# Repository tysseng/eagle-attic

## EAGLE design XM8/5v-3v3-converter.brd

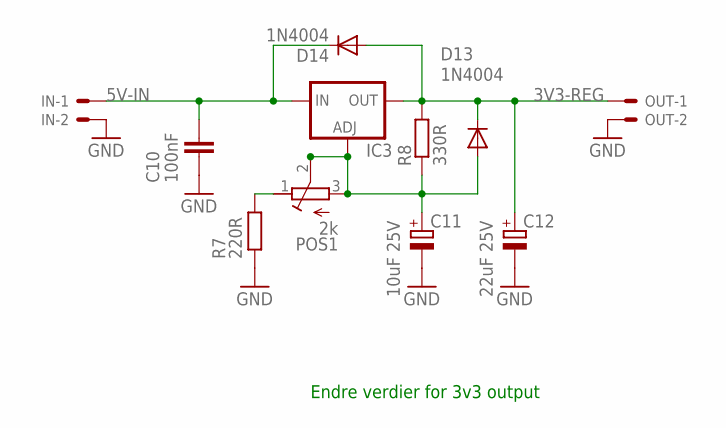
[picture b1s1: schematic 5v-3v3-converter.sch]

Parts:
C10: 100nF; C050-025X075
C11: 10uF 25V; E2,5-5
C12: 22uF 25V; E2,5-5
D13, D14: 1N4004; DO41-10
IC3: LM317TS; 317TS
IN: KK-156-2
OUT: KK-156-2
POS1: 2k; RTRIMT93YA
R7: 220R; 0207/7
R8: 330R; 0207/7

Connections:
3V3-REG: C12.+, D13.C, D14.A, IC3.2 (OUT), OUT.1, R8.2
5V-IN: C10.1, D14.C, IC3.3 (IN), IN.1
GND: C10.2, C11.-, C12.-, IN.2, OUT.2, R7.1
unnamed: POS1.1 (E), R7.2
unnamed: C11.+, D13.A, IC3.1 (ADJ), POS1.2 (S), POS1.3 (A), R8.1

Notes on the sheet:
Endre verdier for 3v3 output

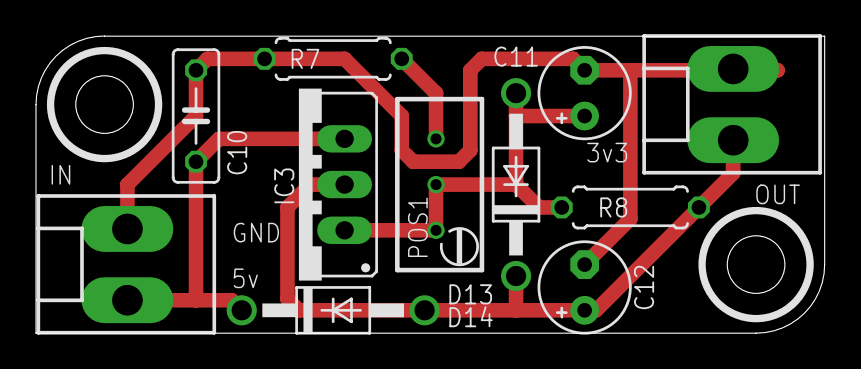
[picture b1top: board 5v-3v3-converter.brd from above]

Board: 2 copper layers, 43.8 x 16.5 mm, 11 parts (0 on the bottom side), 5 nets.

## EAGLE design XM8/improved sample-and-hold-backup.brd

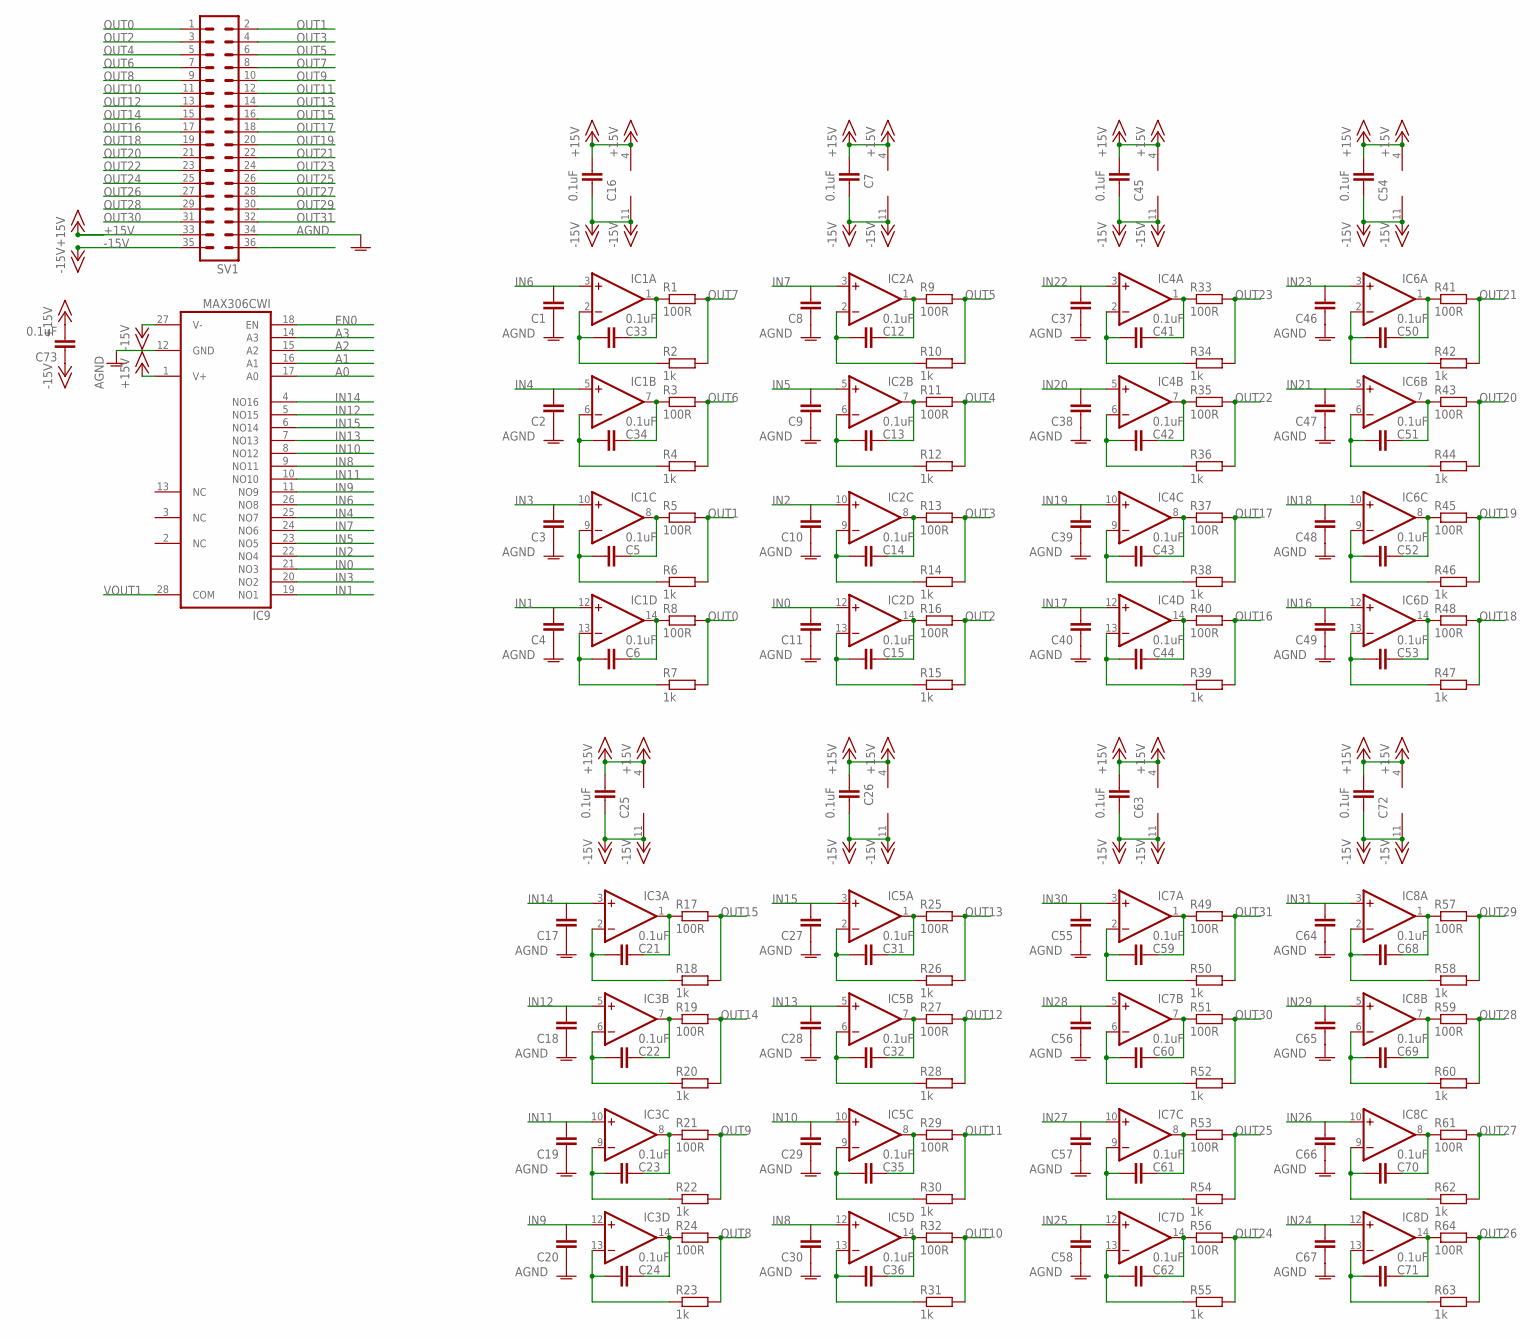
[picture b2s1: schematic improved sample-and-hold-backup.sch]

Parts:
C1, C2, C3, C4, C8, C9, C10, C11, C17, C18, C19, C20, C27, C28, C29, C30, C37, C38, C39, C40, C46, C47, C48, C49, C55, C56, C57, C58, C64, C65, C66, C67: C-EUC1206; C1206
C5, C6, C7, C12, C13, C14, C15, C16, C21, C22, C23, C24, C25, C26, C31, C32, C33, C34, C35, C36, C41, C42, C43, C44, C45, C50, C51, C52, C53, C54, C59, C60, C61, C62, C63, C68, C69, C70, C71, C72, C73: 0.1uF; C0603
IC1, IC2, IC3, IC4, IC5, IC6, IC7, IC8: TL074D; SO14
IC9: MAX306CWI; SO28L
R1, R3, R5, R8, R9, R11, R13, R16, R17, R19, R21, R24, R25, R27, R29, R32, R33, R35, R37, R40, R41, R43, R45, R48, R49, R51, R53, R56, R57, R59, R61, R64: 100R; R0603
R2, R4, R6, R7, R10, R12, R14, R15, R18, R20, R22, R23, R26, R28, R30, R31, R34, R36, R38, R39, R42, R44, R46, R47, R50, R52, R54, R55, R58, R60, R62, R63: 1k; R0603
SV1: MA18-2

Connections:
+15V: C7.1, C16.1, C25.1, C26.1, C45.1, C54.1, C63.1, C72.1, C73.2, IC1.4 (V+), IC2.4 (V+), IC3.4 (V+), IC4.4 (V+), IC5.4 (V+), IC6.4 (V+), IC7.4 (V+), IC8.4 (V+), IC9.1 (V+), SV1.33
-15V: C7.2, C16.2, C25.2, C26.2, C45.2, C54.2, C63.2, C72.2, C73.1, IC1.11 (V-), IC2.11 (V-), IC3.11 (V-), IC4.11 (V-), IC5.11 (V-), IC6.11 (V-), IC7.11 (V-), IC8.11 (V-), IC9.27 (V-), SV1.35
A0: IC9.17 (A0)
A1: IC9.16 (A1)
A2: IC9.15 (A2)
A3: IC9.14 (A3)
AGND: C1.1, C2.1, C3.1, C4.1, C8.1, C9.1, C10.1, C11.1, C17.1, C18.1, C19.1, C20.1, C27.1, C28.1, C29.1, C30.1, C37.1, C38.1, C39.1, C40.1, C46.1, C47.1, C48.1, C49.1, C55.1, C56.1, C57.1, C58.1, C64.1, C65.1, C66.1, C67.1, IC9.12 (GND), SV1.34
EN0: IC9.18 (EN)
IN0: C11.2, IC2.12 (+IN), IC9.21 (NO3)
IN1: C4.2, IC1.12 (+IN), IC9.19 (NO1)
IN2: C10.2, IC2.10 (+IN), IC9.22 (NO4)
IN3: C3.2, IC1.10 (+IN), IC9.20 (NO2)
IN4: C2.2, IC1.5 (+IN), IC9.25 (NO7)
IN5: C9.2, IC2.5 (+IN), IC9.23 (NO5)
IN6: C1.2, IC1.3 (+IN), IC9.26 (NO8)
IN7: C8.2, IC2.3 (+IN), IC9.24 (NO6)
IN8: C30.2, IC5.12 (+IN), IC9.9 (NO11)
IN9: C20.2, IC3.12 (+IN), IC9.11 (NO9)
IN10: C29.2, IC5.10 (+IN), IC9.8 (NO12)
IN11: C19.2, IC3.10 (+IN), IC9.10 (NO10)
IN12: C18.2, IC3.5 (+IN), IC9.5 (NO15)
IN13: C28.2, IC5.5 (+IN), IC9.7 (NO13)
IN14: C17.2, IC3.3 (+IN), IC9.4 (NO16)
IN15: C27.2, IC5.3 (+IN), IC9.6 (NO14)
IN16: C49.2, IC6.12 (+IN)
IN17: C40.2, IC4.12 (+IN)
IN18: C48.2, IC6.10 (+IN)
IN19: C39.2, IC4.10 (+IN)
IN20: C38.2, IC4.5 (+IN)
IN21: C47.2, IC6.5 (+IN)
IN22: C37.2, IC4.3 (+IN)
IN23: C46.2, IC6.3 (+IN)
IN24: C67.2, IC8.12 (+IN)
IN25: C58.2, IC7.12 (+IN)
IN26: C66.2, IC8.10 (+IN)
IN27: C57.2, IC7.10 (+IN)
IN28: C56.2, IC7.5 (+IN)
IN29: C65.2, IC8.5 (+IN)
IN30: C55.2, IC7.3 (+IN)
IN31: C64.2, IC8.3 (+IN)
unnamed: C33.2, IC1.2 (-IN), R2.1
unnamed: C33.1, IC1.1 (OUT), R1.1
unnamed: C34.1, IC1.7 (OUT), R3.1
unnamed: C5.1, IC1.8 (OUT), R5.1
unnamed: C34.2, IC1.6 (-IN), R4.1
unnamed: C6.1, IC1.14 (OUT), R8.1
unnamed: C5.2, IC1.9 (-IN), R6.1
unnamed: C6.2, IC1.13 (-IN), R7.1
unnamed: C21.1, IC3.1 (OUT), R17.1
unnamed: C21.2, IC3.2 (-IN), R18.1
unnamed: C12.1, IC2.1 (OUT), R9.1
unnamed: C12.2, IC2.2 (-IN), R10.1
unnamed: C13.1, IC2.7 (OUT), R11.1
unnamed: C13.2, IC2.6 (-IN), R12.1
unnamed: C14.1, IC2.8 (OUT), R13.1
unnamed: C15.1, IC2.14 (OUT), R16.1
unnamed: C14.2, IC2.9 (-IN), R14.1
unnamed: C15.2, IC2.13 (-IN), R15.1
unnamed: C22.1, IC3.7 (OUT), R19.1
unnamed: C22.2, IC3.6 (-IN), R20.1
unnamed: C23.1, IC3.8 (OUT), R21.1
unnamed: C24.1, IC3.14 (OUT), R24.1
unnamed: C23.2, IC3.9 (-IN), R22.1
unnamed: C24.2, IC3.13 (-IN), R23.1
unnamed: C31.1, IC5.1 (OUT), R25.1
unnamed: C31.2, IC5.2 (-IN), R26.1
unnamed: C32.1, IC5.7 (OUT), R27.1
unnamed: C32.2, IC5.6 (-IN), R28.1
unnamed: C35.1, IC5.8 (OUT), R29.1
unnamed: C36.1, IC5.14 (OUT), R32.1
unnamed: C35.2, IC5.9 (-IN), R30.1
unnamed: C36.2, IC5.13 (-IN), R31.1
unnamed: C41.1, IC4.1 (OUT), R33.1
unnamed: C41.2, IC4.2 (-IN), R34.1
unnamed: C42.1, IC4.7 (OUT), R35.1
unnamed: C42.2, IC4.6 (-IN), R36.1
unnamed: C43.1, IC4.8 (OUT), R37.1
unnamed: C44.1, IC4.14 (OUT), R40.1
unnamed: C43.2, IC4.9 (-IN), R38.1
unnamed: C44.2, IC4.13 (-IN), R39.1
unnamed: C50.1, IC6.1 (OUT), R41.1
unnamed: C50.2, IC6.2 (-IN), R42.1
unnamed: C51.1, IC6.7 (OUT), R43.1
unnamed: C51.2, IC6.6 (-IN), R44.1
unnamed: C52.1, IC6.8 (OUT), R45.1
unnamed: C53.1, IC6.14 (OUT), R48.1
unnamed: C52.2, IC6.9 (-IN), R46.1
unnamed: C53.2, IC6.13 (-IN), R47.1
unnamed: C59.1, IC7.1 (OUT), R49.1
unnamed: C59.2, IC7.2 (-IN), R50.1
unnamed: C60.1, IC7.7 (OUT), R51.1
unnamed: C60.2, IC7.6 (-IN), R52.1
unnamed: C61.1, IC7.8 (OUT), R53.1
unnamed: C62.1, IC7.14 (OUT), R56.1
unnamed: C61.2, IC7.9 (-IN), R54.1
unnamed: C62.2, IC7.13 (-IN), R55.1
unnamed: C68.1, IC8.1 (OUT), R57.1
unnamed: C68.2, IC8.2 (-IN), R58.1
unnamed: C69.1, IC8.7 (OUT), R59.1
unnamed: C69.2, IC8.6 (-IN), R60.1
unnamed: C70.1, IC8.8 (OUT), R61.1
unnamed: C71.1, IC8.14 (OUT), R64.1
unnamed: C70.2, IC8.9 (-IN), R62.1
unnamed: C71.2, IC8.13 (-IN), R63.1
OUT0: R7.2, R8.2, SV1.1
OUT1: R5.2, R6.2, SV1.2
OUT2: R15.2, R16.2, SV1.3
OUT3: R13.2, R14.2, SV1.4
OUT4: R11.2, R12.2, SV1.5
OUT5: R9.2, R10.2, SV1.6
OUT6: R3.2, R4.2, SV1.7
OUT7: R1.2, R2.2, SV1.8
OUT8: R23.2, R24.2, SV1.9
OUT9: R21.2, R22.2, SV1.10
OUT10: R31.2, R32.2, SV1.11
OUT11: R29.2, R30.2, SV1.12
OUT12: R27.2, R28.2, SV1.13
OUT13: R25.2, R26.2, SV1.14
OUT14: R19.2, R20.2, SV1.15
OUT15: R17.2, R18.2, SV1.16
OUT16: R39.2, R40.2, SV1.17
OUT17: R37.2, R38.2, SV1.18
OUT18: R47.2, R48.2, SV1.19
OUT19: R45.2, R46.2, SV1.20
OUT20: R43.2, R44.2, SV1.21
OUT21: R41.2, R42.2, SV1.22
OUT22: R35.2, R36.2, SV1.23
OUT23: R33.2, R34.2, SV1.24
OUT24: R55.2, R56.2, SV1.25
OUT25: R53.2, R54.2, SV1.26
OUT26: R63.2, R64.2, SV1.27
OUT27: R61.2, R62.2, SV1.28
OUT28: R59.2, R60.2, SV1.29
OUT29: R57.2, R58.2, SV1.30
OUT30: R51.2, R52.2, SV1.31
OUT31: R49.2, R50.2, SV1.32
VOUT1: IC9.28 (COM)

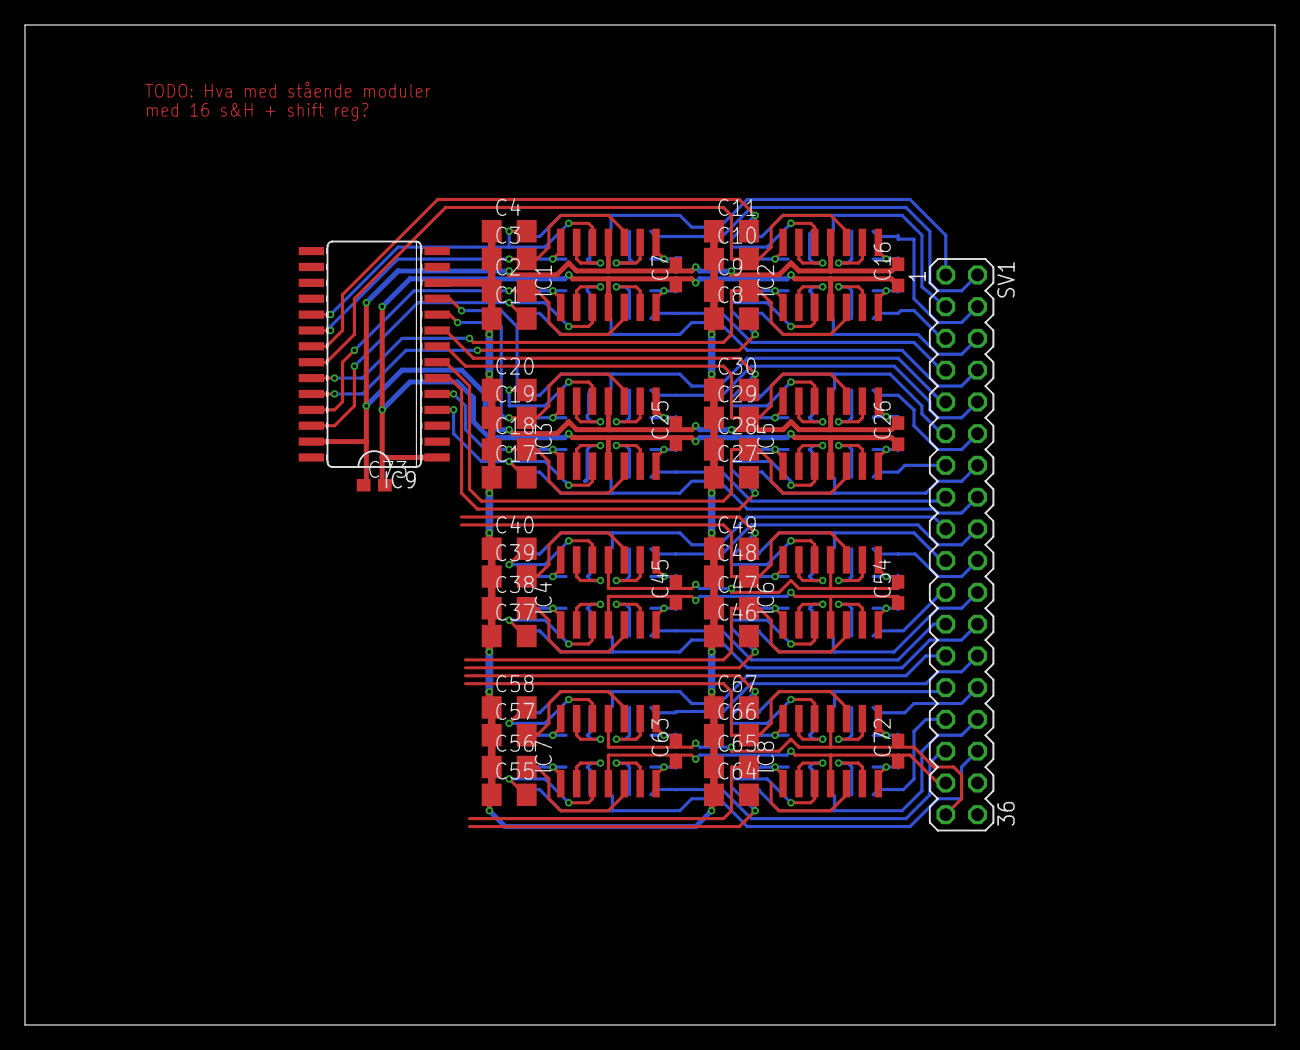
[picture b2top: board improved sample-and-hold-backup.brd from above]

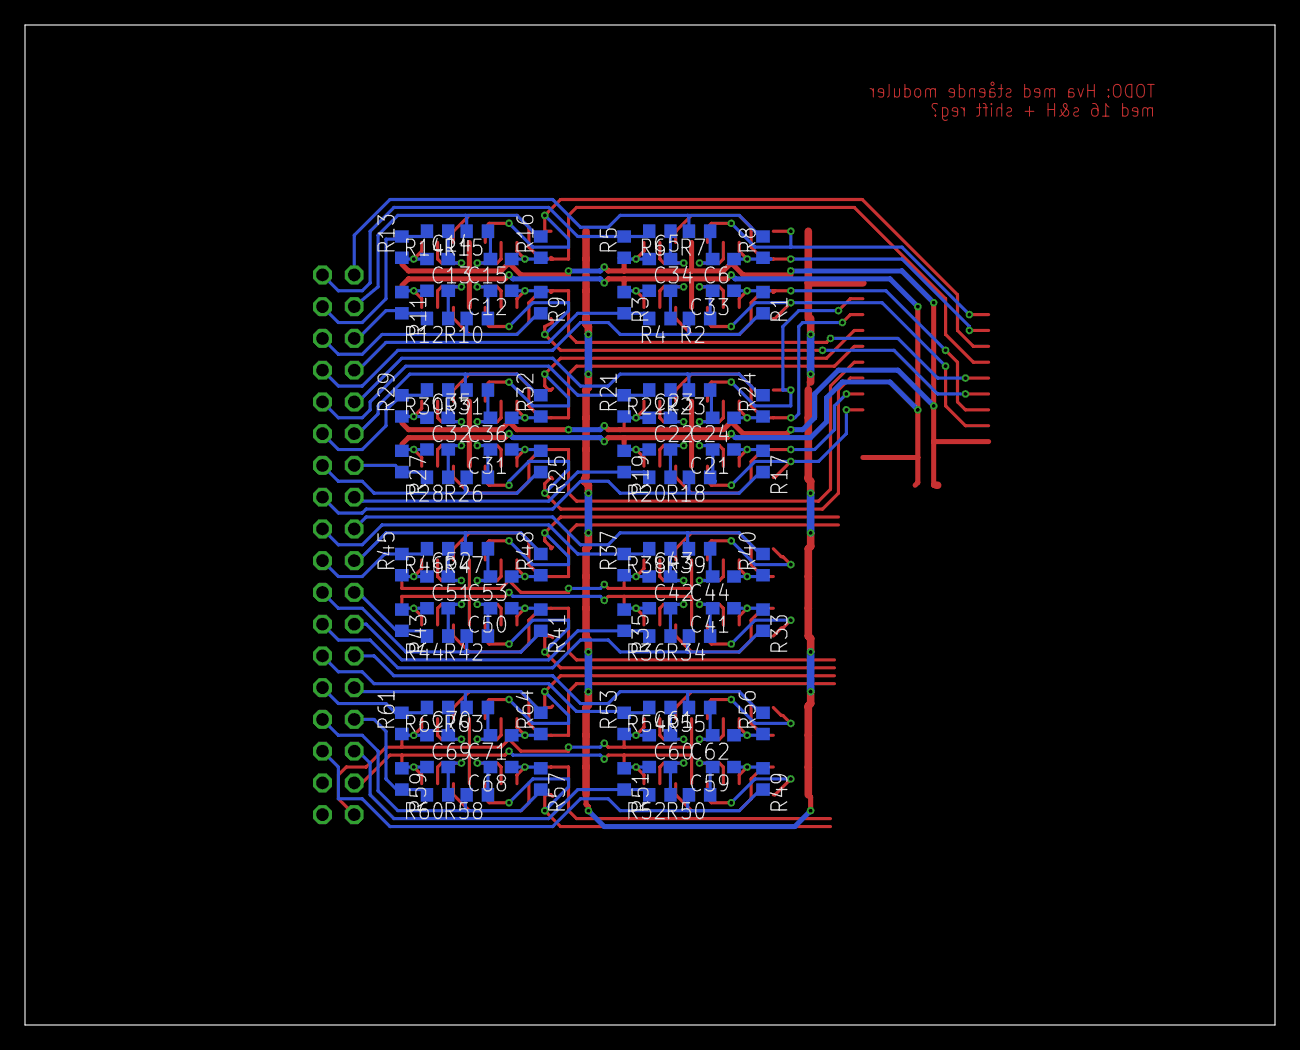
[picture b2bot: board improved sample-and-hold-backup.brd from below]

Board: 2 copper layers, 100.0 x 80.0 mm, 147 parts (96 on the bottom side), 131 nets.

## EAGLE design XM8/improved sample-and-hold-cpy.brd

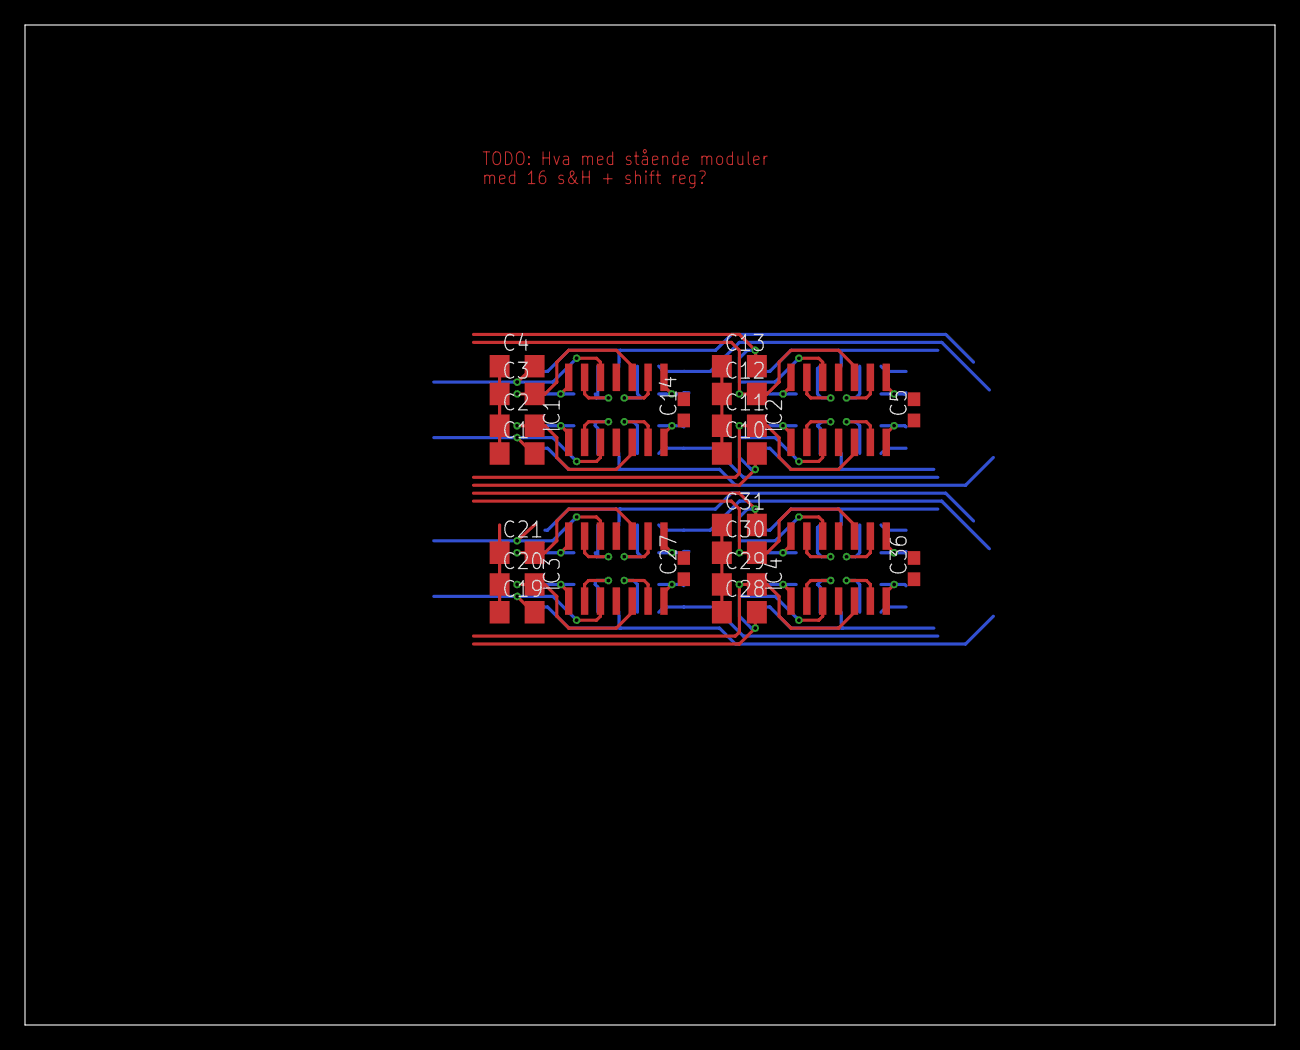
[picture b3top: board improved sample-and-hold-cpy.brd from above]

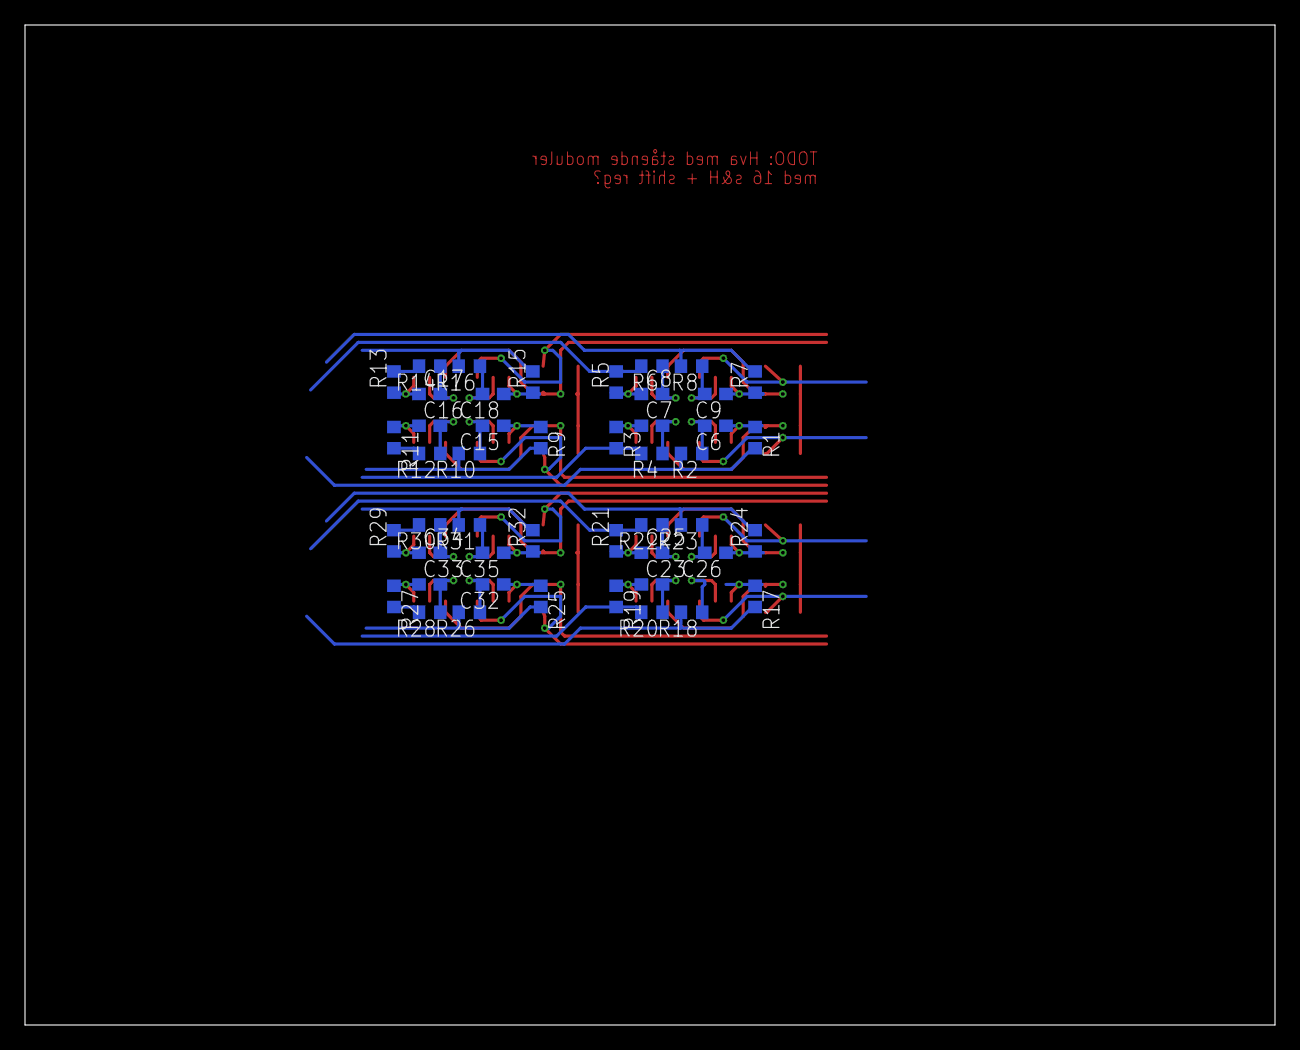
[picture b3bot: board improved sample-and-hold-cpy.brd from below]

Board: 2 copper layers, 100.0 x 80.0 mm, 70 parts (47 on the bottom side), 69 nets.

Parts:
C1, C2, C3, C4, C10, C11, C12, C13, C19, C20, C21, C28, C29, C30, C31: C1206
C5, C6, C7, C8, C9, C14, C15, C16, C17, C18, C23, C25, C26, C27, C32, C33, C34, C35, C36: 0.1uF; C0603
IC1, IC2, IC3, IC4: TL074D; SO14
R1, R3, R5, R7, R9, R11, R13, R15, R17, R19, R21, R24, R25, R27, R29, R32: 100R; R0603
R2, R4, R6, R8, R10, R12, R14, R16, R18, R20, R22, R23, R26, R28, R30, R31: 1k; R0603

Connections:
+15V: C5.1, C14.1, IC1.4, IC2.4
+15V1: C27.1, C36.1, IC3.4, IC4.4
-15V: C5.2, C14.2, IC1.11, IC2.11
-15V1: C27.2, C36.2, IC3.11, IC4.11
AGND: C1.1, C2.1, C3.1, C4.1, C10.1, C11.1, C12.1, C13.1
AGND1: C19.1, C20.1, C21.1, C28.1, C29.1, C30.1, C31.1
IN0: C13.2, IC2.12
IN1: C4.2, IC1.12
IN2: C12.2, IC2.10
IN3: C3.2, IC1.10
IN4: C2.2, IC1.5
IN5: C11.2, IC2.5
IN6: C1.2, IC1.3
IN7: C10.2, IC2.3
IN9: C21.2, IC3.10
IN10: C20.2, IC3.5
IN11: C19.2, IC3.3
IN12: C28.2, IC4.3
IN13: C29.2, IC4.5
IN14: C30.2, IC4.10
IN15: C31.2, IC4.12
unnamed: C6.2, IC1.2, R2.1
unnamed: C6.1, IC1.1, R1.1
unnamed: C7.1, IC1.7, R3.1
unnamed: C8.1, IC1.8, R5.1
unnamed: C7.2, IC1.6, R4.1
unnamed: C9.1, IC1.14, R7.1
unnamed: C8.2, IC1.9, R6.1
unnamed: C9.2, IC1.13, R8.1
unnamed: IC3.1, R17.1
unnamed: IC3.2, R18.1
unnamed: C15.1, IC2.1, R9.1
unnamed: C15.2, IC2.2, R10.1
unnamed: C16.1, IC2.7, R11.1
unnamed: C16.2, IC2.6, R12.1
unnamed: C17.1, IC2.8, R13.1
unnamed: C18.1, IC2.14, R15.1
unnamed: C17.2, IC2.9, R14.1
unnamed: C18.2, IC2.13, R16.1
unnamed: C23.1, IC3.7, R19.1
unnamed: C23.2, IC3.6, R20.1
unnamed: C25.1, IC3.8, R21.1
unnamed: C26.1, IC3.14, R24.1
unnamed: C25.2, IC3.9, R22.1
unnamed: C26.2, IC3.13, R23.1
unnamed: C32.1, IC4.1, R25.1
unnamed: C32.2, IC4.2, R26.1
unnamed: C33.1, IC4.7, R27.1
unnamed: C33.2, IC4.6, R28.1
unnamed: C34.1, IC4.8, R29.1
unnamed: C35.1, IC4.14, R32.1
unnamed: C34.2, IC4.9, R30.1
unnamed: C35.2, IC4.13, R31.1
OUT0: R15.2, R16.2
OUT1: R7.2, R8.2
OUT2: R13.2, R14.2
OUT3: R5.2, R6.2
OUT4: R3.2, R4.2
OUT5: R11.2, R12.2
OUT6: R1.2, R2.2
OUT7: R9.2, R10.2
OUT8: R23.2, R24.2
OUT9: R21.2, R22.2
OUT10: R19.2, R20.2
OUT11: R17.2, R18.2
OUT12: R31.2, R32.2
OUT13: R29.2, R30.2
OUT14: R27.2, R28.2
OUT15: R25.2, R26.2

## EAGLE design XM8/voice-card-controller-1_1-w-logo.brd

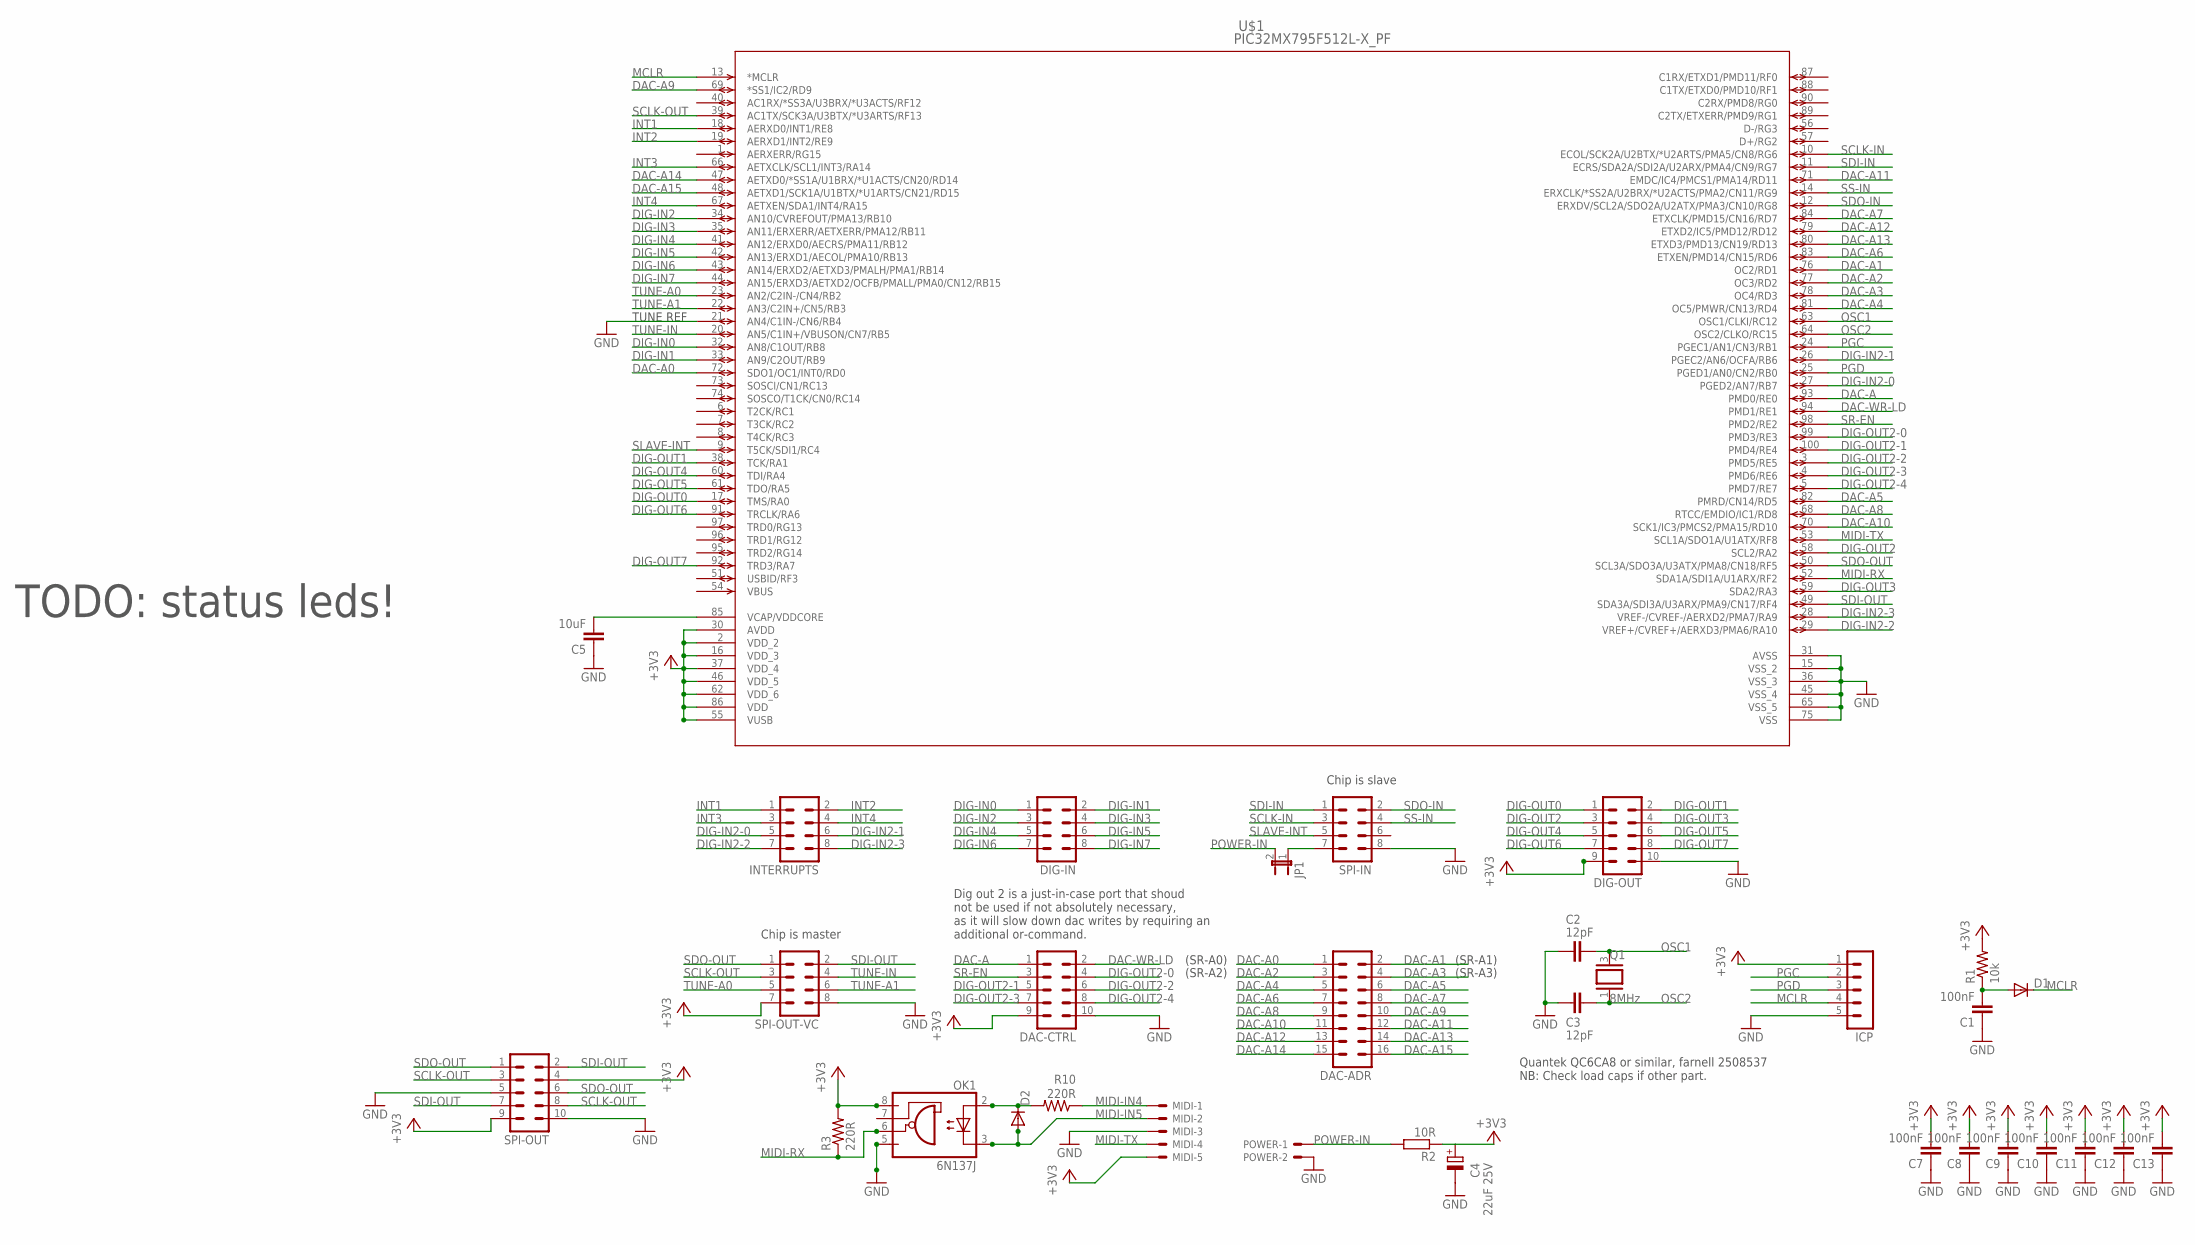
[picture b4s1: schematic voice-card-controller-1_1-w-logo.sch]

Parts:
C1, C7, C8, C9, C10, C11, C12, C13: 100nF; C0603
C2, C3: 12pF; C0603
C4: 22uF 25V; E2,5-5
C5: 10uF; C0805
D1, D2: DIODE-SOD80C; SOD80C
DAC-ADR: MA08-2J
DAC-CTRL: MA05-2J
DIG-IN: MA04-2J
DIG-OUT: MA05-2J
ICP: MA05-1
INTERRUPTS: MA04-2J
JP1: JP1E; JP1
MIDI: 22-23-2051
OK1: 6N137J; DIL08-J
POWER: 22-23-2021
Q1: 8MHz; CTS406J
R1: 10k; R0805
R2: 10R; 0207/7
R3, R10: 220R; R0805
SPI-IN: MA04-2J
SPI-OUT: MA05-2J
SPI-OUT-VC: MA04-2J
U$1: PIC32MX795F512L-X_PF; TQFP100_14X14MC

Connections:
+3V3: C4.+, C7.2, C8.2, C9.2, C10.2, C11.2, C12.2, C13.2, DAC-CTRL.9, DIG-OUT.9, ICP.1, MIDI.5, OK1.8 (VCC), R1.2, R2.1, R3.2, SPI-OUT.4, SPI-OUT.9, SPI-OUT-VC.7, U$1.2 (VDD_2), U$1.16 (VDD_3), U$1.30 (AVDD), U$1.37 (VDD_4), U$1.46 (VDD_5), U$1.55 (VUSB), U$1.62 (VDD_6), U$1.86 (VDD)
DAC-A: DAC-CTRL.1, U$1.93 (PMD0/RE0)
DAC-A0: DAC-ADR.1, U$1.72 (SDO1/OC1/INT0/RD0)
DAC-A1: DAC-ADR.2, U$1.76 (OC2/RD1)
DAC-A2: DAC-ADR.3, U$1.77 (OC3/RD2)
DAC-A3: DAC-ADR.4, U$1.78 (OC4/RD3)
DAC-A4: DAC-ADR.5, U$1.81 (OC5/PMWR/CN13/RD4)
DAC-A5: DAC-ADR.6, U$1.82 (PMRD/CN14/RD5)
DAC-A6: DAC-ADR.7, U$1.83 (ETXEN/PMD14/CN15/RD6)
DAC-A7: DAC-ADR.8, U$1.84 (ETXCLK/PMD15/CN16/RD7)
DAC-A8: DAC-ADR.9, U$1.68 (RTCC/EMDIO/IC1/RD8)
DAC-A9: DAC-ADR.10, U$1.69 (*SS1/IC2/RD9)
DAC-A10: DAC-ADR.11, U$1.70 (SCK1/IC3/PMCS2/PMA15/RD10)
DAC-A11: DAC-ADR.12, U$1.71 (EMDC/IC4/PMCS1/PMA14/RD11)
DAC-A12: DAC-ADR.13, U$1.79 (ETXD2/IC5/PMD12/RD12)
DAC-A13: DAC-ADR.14, U$1.80 (ETXD3/PMD13/CN19/RD13)
DAC-A14: DAC-ADR.15, U$1.47 (AETXD0/*SS1A/U1BRX/*U1ACTS/CN20/RD14)
DAC-A15: DAC-ADR.16, U$1.48 (AETXD1/SCK1A/U1BTX/*U1ARTS/CN21/RD15)
DAC-WR-LD: DAC-CTRL.2, U$1.94 (PMD1/RE1)
DIG-IN0: DIG-IN.1, U$1.32 (AN8/C1OUT/RB8)
DIG-IN1: DIG-IN.2, U$1.33 (AN9/C2OUT/RB9)
DIG-IN2: DIG-IN.3, U$1.34 (AN10/CVREFOUT/PMA13/RB10)
DIG-IN2-0: INTERRUPTS.5, U$1.27 (PGED2/AN7/RB7)
DIG-IN2-1: INTERRUPTS.6, U$1.26 (PGEC2/AN6/OCFA/RB6)
DIG-IN2-2: INTERRUPTS.7, U$1.29 (VREF+/CVREF+/AERXD3/PMA6/RA10)
DIG-IN2-3: INTERRUPTS.8, U$1.28 (VREF-/CVREF-/AERXD2/PMA7/RA9)
DIG-IN3: DIG-IN.4, U$1.35 (AN11/ERXERR/AETXERR/PMA12/RB11)
DIG-IN4: DIG-IN.5, U$1.41 (AN12/ERXD0/AECRS/PMA11/RB12)
DIG-IN5: DIG-IN.6, U$1.42 (AN13/ERXD1/AECOL/PMA10/RB13)
DIG-IN6: DIG-IN.7, U$1.43 (AN14/ERXD2/AETXD3/PMALH/PMA1/RB14)
DIG-IN7: DIG-IN.8, U$1.44 (AN15/ERXD3/AETXD2/OCFB/PMALL/PMA0/CN12/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)
DIG-OUT0: DIG-OUT.1, U$1.17 (TMS/RA0)
DIG-OUT1: DIG-OUT.2, U$1.38 (TCK/RA1)
DIG-OUT2: DIG-OUT.3, U$1.58 (SCL2/RA2)
DIG-OUT2-0: DAC-CTRL.4, U$1.99 (PMD3/RE3)
DIG-OUT2-1: DAC-CTRL.5, U$1.100 (PMD4/RE4)
DIG-OUT2-2: DAC-CTRL.6, U$1.3 (PMD5/RE5)
DIG-OUT2-3: DAC-CTRL.7, U$1.4 (PMD6/RE6)
DIG-OUT2-4: DAC-CTRL.8, U$1.5 (PMD7/RE7)
DIG-OUT3: DIG-OUT.4, U$1.59 (SDA2/RA3)
DIG-OUT4: DIG-OUT.5, U$1.60 (TDI/RA4)
DIG-OUT5: DIG-OUT.6, U$1.61 (TDO/RA5)
DIG-OUT6: DIG-OUT.7, U$1.91 (TRCLK/RA6)
DIG-OUT7: DIG-OUT.8, U$1.92 (TRD3/RA7)
GND: C1.1, C2.2, C3.2, C4.-, C5.1, C7.1, C8.1, C9.1, C10.1, C11.1, C12.1, C13.1, DAC-CTRL.10, DIG-OUT.10, ICP.5, MIDI.3, OK1.5 (GND), POWER.2, SPI-IN.8, SPI-OUT.5, SPI-OUT.10, SPI-OUT-VC.8, U$1.15 (VSS_2), U$1.21 (AN4/C1IN-/CN6/RB4), U$1.31 (AVSS), U$1.36 (VSS_3), U$1.45 (VSS_4), U$1.65 (VSS_5), U$1.75 (VSS)
INT1: INTERRUPTS.1, U$1.18 (AERXD0/INT1/RE8)
INT2: INTERRUPTS.2, U$1.19 (AERXD1/INT2/RE9)
INT3: INTERRUPTS.3, U$1.66 (AETXCLK/SCL1/INT3/RA14)
INT4: INTERRUPTS.4, U$1.67 (AETXEN/SDA1/INT4/RA15)
MCLR: D1.C, ICP.4, U$1.13 (*MCLR)
MIDI-IN4: MIDI.1, R10.1
MIDI-IN5: D2.A, MIDI.2, OK1.3 (C)
MIDI-RX: OK1.6 (VO), R3.1, U$1.52 (SDA1A/SDI1A/U1ARX/RF2)
MIDI-TX: MIDI.4, U$1.53 (SCL1A/SDO1A/U1ATX/RF8)
unnamed: C5.2, U$1.85 (VCAP/VDDCORE)
unnamed: JP1.1, SPI-IN.7
unnamed: C1.2, D1.A, R1.1
unnamed: D2.C, OK1.2 (A), R10.2
OSC1: C2.1, Q1.3 (2), U$1.63 (OSC1/CLKI/RC12)
OSC2: C3.1, Q1.1, U$1.64 (OSC2/CLKO/RC15)
PGC: ICP.2, U$1.24 (PGEC1/AN1/CN3/RB1)
PGD: ICP.3, U$1.25 (PGED1/AN0/CN2/RB0)
POWER-IN: JP1.2, POWER.1, R2.2
SCLK-IN: SPI-IN.3, U$1.10 (ECOL/SCK2A/U2BTX/*U2ARTS/PMA5/CN8/RG6)
SCLK-OUT: SPI-OUT.3, SPI-OUT.8, SPI-OUT-VC.3, U$1.39 (AC1TX/SCK3A/U3BTX/*U3ARTS/RF13)
SDI-IN: SPI-IN.1, U$1.11 (ECRS/SDA2A/SDI2A/U2ARX/PMA4/CN9/RG7)
SDI-OUT: SPI-OUT.2, SPI-OUT.7, SPI-OUT-VC.2, U$1.49 (SDA3A/SDI3A/U3ARX/PMA9/CN17/RF4)
SDO-IN: SPI-IN.2, U$1.12 (ERXDV/SCL2A/SDO2A/U2ATX/PMA3/CN10/RG8)
SDO-OUT: SPI-OUT.1, SPI-OUT.6, SPI-OUT-VC.1, U$1.50 (SCL3A/SDO3A/U3ATX/PMA8/CN18/RF5)
SLAVE-INT: SPI-IN.5, U$1.9 (T5CK/SDI1/RC4)
SR-EN: DAC-CTRL.3, U$1.98 (PMD2/RE2)
SS-IN: SPI-IN.4, U$1.14 (ERXCLK/*SS2A/U2BRX/*U2ACTS/PMA2/CN11/RG9)
TUNE-A0: SPI-OUT-VC.5, U$1.23 (AN2/C2IN-/CN4/RB2)
TUNE-A1: SPI-OUT-VC.6, U$1.22 (AN3/C2IN+/CN5/RB3)
TUNE-IN: SPI-OUT-VC.4, U$1.20 (AN5/C1IN+/VBUSON/CN7/RB5)

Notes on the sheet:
(SR-A0)
(SR-A2)
(SR-A1)
(SR-A3)
Chip is slave
Chip is master
TUNE REF
Dig out 2 is a just-in-case port that shoud not be used if not absolutely necessary, as it will slow down dac writes by requiring an additional or-command.
Quantek QC6CA8 or similar, farnell 2508537 NB: Check load caps if other part.
TODO: status leds!

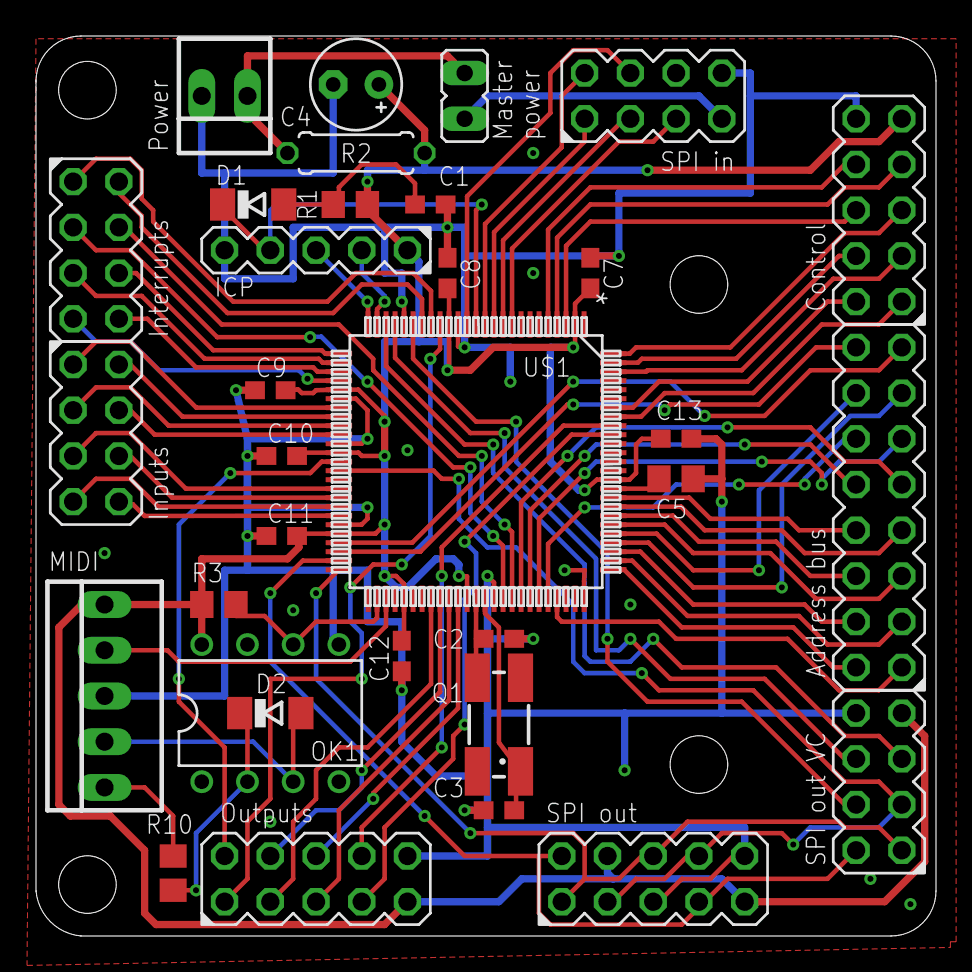
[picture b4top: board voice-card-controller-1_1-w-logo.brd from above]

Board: 2 copper layers, 50.0 x 50.0 mm, 33 parts (0 on the bottom side), 75 nets.

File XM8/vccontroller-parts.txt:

Partlist

Exported from voice-card-controller-1_1.sch at 09.04.2016 21:07:20

EAGLE Version 7.2.0 Copyright (c) 1988-2014 CadSoft

Assembly variant: 

Part       Value                Device               Package         Library           Sheet

C1         100nF                C-EUC0603            C0603           resistor          1
C2         12pF                 C-EUC0603            C0603           resistor          1
C3         12pF                 C-EUC0603            C0603           resistor          1
C4         22uF 25V             CPOL-EUE2.5-5        E2,5-5          resistor          1
C5         10uF                 C-EUC0805            C0805           resistor          1
C7         100nF                C-EUC0603            C0603           resistor          1
C8         100nF                C-EUC0603            C0603           resistor          1
C9         100nF                C-EUC0603            C0603           resistor          1
C10        100nF                C-EUC0603            C0603           resistor          1
C11        100nF                C-EUC0603            C0603           resistor          1
C12        100nF                C-EUC0603            C0603           resistor          1
C13        100nF                C-EUC0603            C0603           resistor          1
D1                              DIODE-SOD80C         SOD80C          diode             1
D2                              DIODE-SOD80C         SOD80C          diode             1
DAC-ADR                         MA08-2J              MA08-2J         joakim            1
DAC-CTRL                        MA05-2J              MA05-2J         joakim            1
DIG-IN                          MA04-2J              MA04-2J         joakim            1
DIG-OUT                         MA05-2J              MA05-2J         joakim            1
ICP                             MA05-1               MA05-1          joakim            1
INTERRUPTS                      MA04-2J              MA04-2J         joakim            1
JP1                             JP1E                 JP1             jumper            1
MIDI       22-23-2051           22-23-2051           22-23-2051      con-molex         1
OK1        6N137J               6N137J               DIL08-J         joakim            1
POWER      22-23-2021           22-23-2021           22-23-2021      con-molex         1
Q1         8MHz                 XTAL-J               CTS406J         joakim            1
R1         10k                  R-US_R0805           R0805           resistor          1
R2         10R                  R-EU_0207/7          0207/7          resistor          1
R3         220R                 R-US_R0805           R0805           resistor          1
R10        220R                 R-US_R0805           R0805           resistor          1
SPI-IN                          MA04-2J              MA04-2J         joakim            1
SPI-OUT                         MA05-2J              MA05-2J         joakim            1
SPI-OUT-VC                      MA04-2J              MA04-2J         joakim            1
U$1        PIC32MX795F512L-X_PF PIC32MX795F512L-X_PF TQFP100_14X14MC pic32mx-795F-512L 1
